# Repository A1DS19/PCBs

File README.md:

# PCB Designs

A collection of printed circuit board (PCB) designs for various projects.

## Overview

This repository contains PCB design files, schematics, and documentation for custom electronic circuits.

## PCB Process:
1. Place components
2. Create board outline (Edge.Cuts)
3. Export DSN to Freerouting
4. Autoroute in Freerouting
5. Import SES file back to KiCad
6. THEN add copper pours (last step!)
7. Fill zones (B key)
8. Add vias for ground plane stitching
9. Run final DRC

## Getting Started

### Prerequisites
- [KiCad](https://www.kicad.org/) - Open source EDA software

### Manufacturing
- [JLCPCB](https://jlcpcb.com/)

- Vid: 3:36:29

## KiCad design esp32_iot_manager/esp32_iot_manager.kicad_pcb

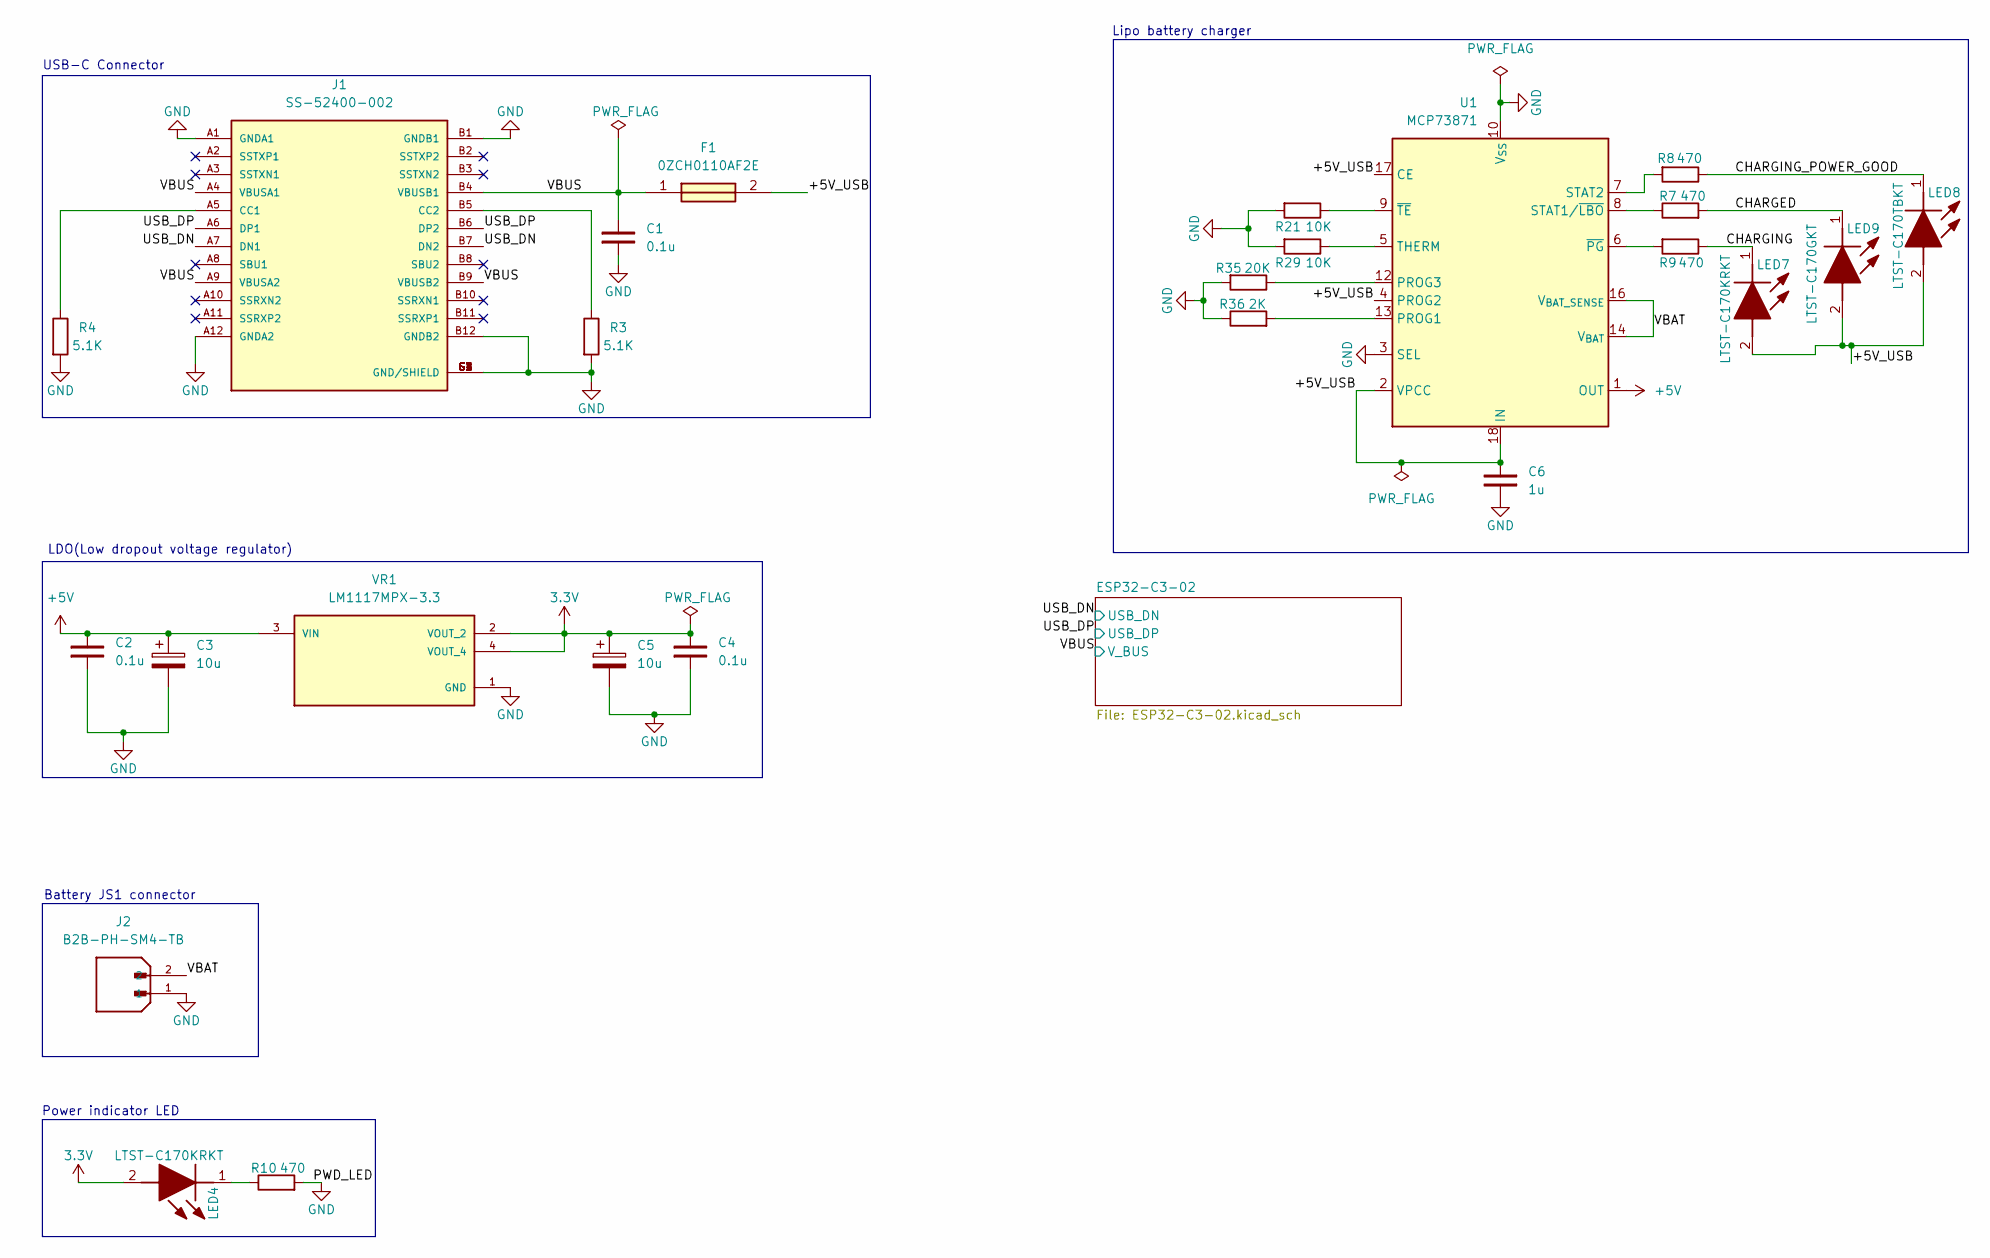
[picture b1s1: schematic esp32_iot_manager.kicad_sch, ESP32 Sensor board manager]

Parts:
C1, C2, C4: 0.1u; C_0805_2012Metric
C3, C5: 10u; T491A
C6: 1u; C_Disc_D3.0mm_W2.0mm_P2.50mm
F1: 0ZCH0110AF2E; FUSC3226X100N; Manufacturer_Part_Number 0ZCH0110AF2E
J1: SS-52400-002; BELFUSE_SS-52400-002; PARTREV A0
J2: B2B-PH-SM4-TB; JST_B2B-PH-SM4-TB; PARTREV N/A
LED4, LED7: LTST-C170KRKT; LEDC2012X120N; Manufacturer_Part_Number LTST-C170KRKT; Mouser Part Number 859-LTST-C170KRKT
LED8: LTST-C170TBKT; LEDC2012X120N; Manufacturer_Part_Number LTST-C170TBKT; Mouser Part Number 859-LTST-C170TBKT
LED9: LTST-C170GKT; LEDC2012X120N; Manufacturer_Part_Number LTST-C170GKT; Mouser Part Number 859-LTST-C170GKT
R3, R4: 5.1K; R_0805_2012Metric
R7, R8, R9, R10: 470; R_0805_2012Metric
R21, R29: 10K; R_0805_2012Metric
R35: 20K; R_0805_2012Metric
R36: 2K; R_0805_2012Metric
U1: MCP73871; QFN-20-1EP_4x4mm_P0.5mm_EP2.5x2.5mm
VR1: LM1117MPX-3.3; VREG_LM1117MPX-3.3

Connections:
3.3V: C4.2, C5.1, LED4.2 (A), VR1.2 (VOUT_2), VR1.4 (VOUT_4); also elsewhere on the board
+5V: C2.2, C3.1, U1.1 (OUT), U1.20 (OUT), VR1.3 (VIN); also elsewhere on the board
/+5V_USB: C6.1, F1.2, LED7.2 (A), LED8.2 (A), LED9.2 (A), U1.2 (VPCC), U1.4 (PROG2), U1.17 (CE), U1.18 (IN), U1.19 (IN)
/CHARGED: LED9.1 (K), R7.2
/CHARGING: LED7.1 (K), R9.1
/CHARGING_POWER_GOOD: LED8.1 (K), R8.1
/USB_DN: J1.A7 (DN1), J1.B7 (DN2); also elsewhere on the board
/USB_DP: J1.A6 (DP1), J1.B6 (DP2); also elsewhere on the board
/VBAT: J2.2, U1.14 (V_{BAT}), U1.15 (V_{BAT}), U1.16 (V_{BAT_SENSE})
/VBUS: C1.2, F1.1, J1.A4 (VBUSA1), J1.A9 (VBUSA2), J1.B4 (VBUSB1), J1.B9 (VBUSB2); also elsewhere on the board
GND: C1.1, C2.1, C3.2, C4.1, C5.2, C6.2, J1.A1 (GNDA1), J1.A12 (GNDA2), J1.B1 (GNDB1), J1.B12 (GNDB2), J1.G1 (GND/SHIELD), J1.G2 (GND/SHIELD), J1.G3 (GND/SHIELD), J1.G4 (GND/SHIELD), J1.S1 (GND/SHIELD), J1.S2 (GND/SHIELD), J1.S3 (GND/SHIELD), J1.S4 (GND/SHIELD), J2.1, R3.2, R4.2, R10.2, R21.2, R29.2, R35.2, R36.1, U1.3 (SEL), U1.10 (V_{SS}), U1.11 (V_{SS}), U1.21 (V_{SS}), VR1.1 (GND); also elsewhere on the board
unnamed: J1.A5 (CC1), R4.1
unnamed: J1.B5 (CC2), R3.1
unnamed: LED4.1 (K), R10.1
unnamed: R36.2, U1.13 (PROG1)
unnamed: R35.1, U1.12 (PROG3)
unnamed: R7.1, U1.8 (STAT1/~LBO)
unnamed: R8.2, U1.7 (STAT2)
unnamed: R29.1, U1.5 (THERM)
unnamed: R9.2, U1.6 (~PG)
unnamed: R21.1, U1.9 (~TE)

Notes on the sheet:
Battery JS1 connector
Power indicator LED
Lipo battery charger
USB-C Connector
LDO(Low dropout voltage regulator)

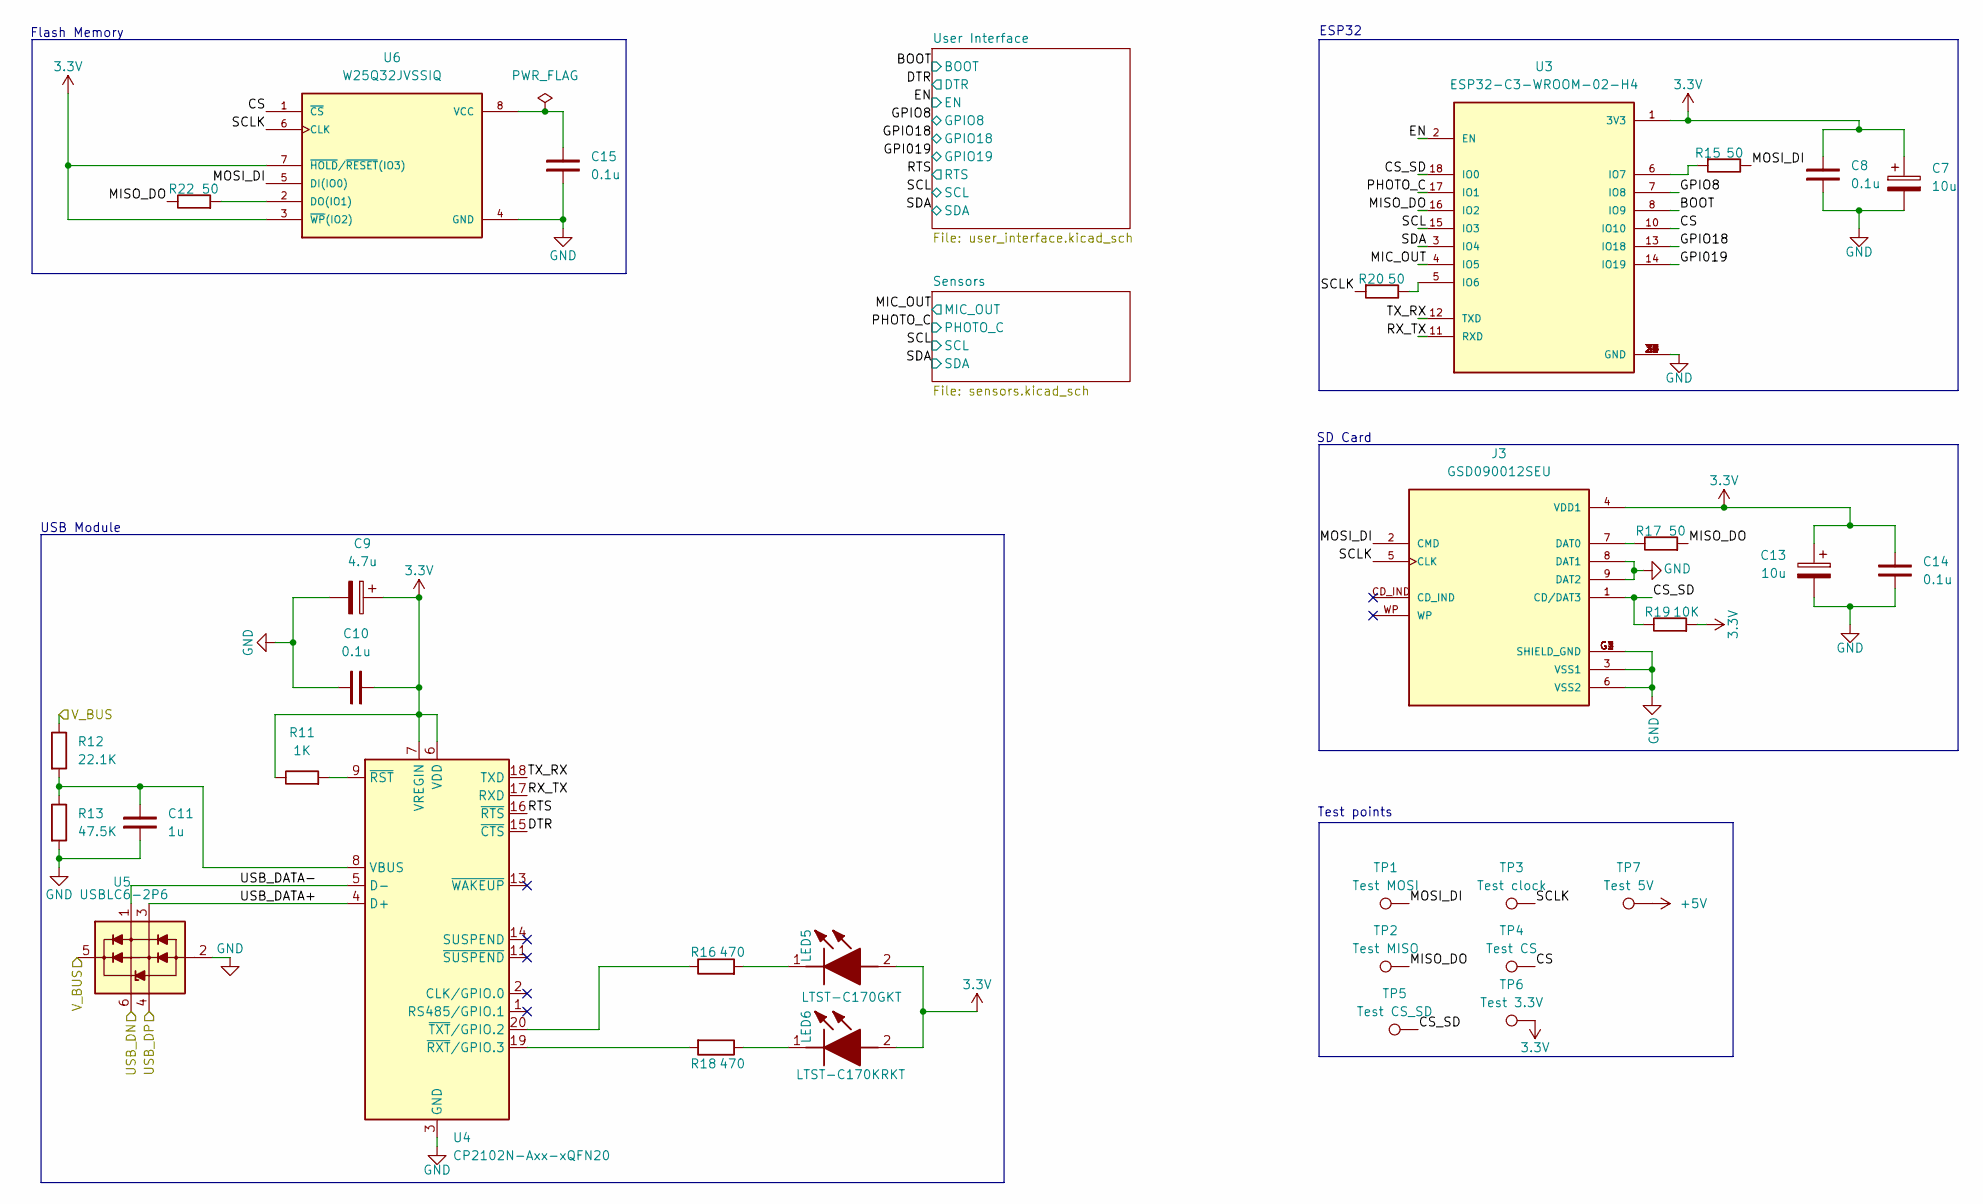
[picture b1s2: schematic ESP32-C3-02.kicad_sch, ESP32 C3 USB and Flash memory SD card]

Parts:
C7, C13: 10u; T491A
C8, C10, C14, C15: 0.1u; C_0805_2012Metric
C9: 4.7u; T491A
C11: 1u; C_0805_2012Metric
J3: GSD090012SEU; AMPHENOL_GSD090012SEU; PARTREV E
LED5: LTST-C170GKT; LEDC2012X120N; Manufacturer_Part_Number LTST-C170GKT; Mouser Part Number 859-LTST-C170GKT
LED6: LTST-C170KRKT; LEDC2012X120N; Manufacturer_Part_Number LTST-C170KRKT; Mouser Part Number 859-LTST-C170KRKT
R11: 1K; R_0805_2012Metric
R12: 22.1K; R_0805_2012Metric
R13: 47.5K; R_0805_2012Metric
R15, R17, R20, R22: 50; R_0805_2012Metric
R16, R18: 470; R_0805_2012Metric
R19: 10K; R_0805_2012Metric
TP1: Test MOSI; TestPoint_Pad_D1.0mm
TP2: Test MISO; TestPoint_Pad_D1.0mm
TP3: Test clock; TestPoint_Pad_D1.0mm
TP4: Test CS; TestPoint_Pad_D1.0mm
TP5: Test CS_SD; TestPoint_Pad_D1.0mm
TP6: Test 3.3V; TestPoint_Pad_D1.0mm
TP7: Test 5V; TestPoint_Pad_D1.0mm
U3: ESP32-C3-WROOM-02-H4; MODULE_ESP32-C3-WROOM-02-H4
U4: CP2102N-Axx-xQFN20; SiliconLabs_QFN-20-1EP_3x3mm_P0.5mm
U5: USBLC6-2P6; SOT-666
U6: W25Q32JVSSIQ; SOIC127P790X216-8N; M_PART_NUMBER W25QXX

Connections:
3.3V: C7.1, C8.2, C9.1, C10.1, C13.1, C14.1, J3.4 (VDD1), LED5.2 (A), LED6.2 (A), R11.2, R19.1, TP6.1, U3.1 (3V3), U4.6 (VDD), U4.7 (VREGIN), U6.3 (~WP(IO2)), U6.7 (~HOLD/~RESET(IO3)); also elsewhere on the board
+5V: TP7.1; also elsewhere on the board
/ESP32-C3-02/BOOT: U3.8 (IO9); also elsewhere on the board
/ESP32-C3-02/CS: TP4.1, U3.10 (IO10), U6.1 (~CS)
/ESP32-C3-02/CS_SD: J3.1 (CD/DAT3), R19.2, TP5.1, U3.18 (IO0)
/ESP32-C3-02/DTR: U4.15 (~CTS); also elsewhere on the board
/ESP32-C3-02/EN: U3.2 (EN); also elsewhere on the board
/ESP32-C3-02/GPI019: U3.14 (IO19); also elsewhere on the board
/ESP32-C3-02/GPIO8: U3.7 (IO8); also elsewhere on the board
/ESP32-C3-02/GPIO18: U3.13 (IO18); also elsewhere on the board
/ESP32-C3-02/MIC_OUT: U3.4 (IO5); also elsewhere on the board
/ESP32-C3-02/MISO_DO: R17.1, R22.2, TP2.1, U3.16 (IO2)
/ESP32-C3-02/MOSI_DI: J3.2 (CMD), R15.2, TP1.1, U6.5 (DI(IO0))
/ESP32-C3-02/PHOTO_C: U3.17 (IO1); also elsewhere on the board
/ESP32-C3-02/RTS: U4.16 (~RTS); also elsewhere on the board
/ESP32-C3-02/RX_TX: U3.11 (RXD), U4.17 (RXD)
/ESP32-C3-02/SCL: U3.15 (IO3); also elsewhere on the board
/ESP32-C3-02/SCLK: J3.5 (CLK), R20.1, TP3.1, U6.6 (CLK)
/ESP32-C3-02/SDA: U3.3 (IO4); also elsewhere on the board
/ESP32-C3-02/TX_RX: U3.12 (TXD), U4.18 (TXD)
/ESP32-C3-02/USB_DATA+: U4.4 (D+), U5.3 (L2)
/ESP32-C3-02/USB_DATA-: U4.5 (D-), U5.1 (L1)
/USB_DN: U5.6 (L1); also elsewhere on the board
/USB_DP: U5.4 (L2); also elsewhere on the board
/VBUS: R12.1, U5.5 (VP); also elsewhere on the board
GND: C7.2, C8.1, C9.2, C10.2, C11.1, C13.2, C14.2, C15.1, J3.3 (VSS1), J3.6 (VSS2), J3.8 (DAT1), J3.9 (DAT2), J3.G1 (SHIELD_GND), J3.G2 (SHIELD_GND), J3.G3 (SHIELD_GND), J3.G4 (SHIELD_GND), R13.2, U3.9 (GND), U3.19 (GND), U3.20 (GND), U3.21 (GND), U3.22 (GND), U3.23 (GND), U3.24 (GND), U3.25 (GND), U3.26 (GND), U3.27 (GND), U3.28 (GND), U3.29 (GND), U3.30 (GND), U3.31 (GND), U3.32 (GND), U3.33 (GND), U3.34 (GND), U3.35 (GND), U3.36 (GND), U3.37 (GND), U3.38 (GND), U3.39 (GND), U4.3 (GND), U4.12 (GND), U4.21 (GND), U5.2 (VN), U6.4 (GND); also elsewhere on the board
unnamed: J3.7 (DAT0), R17.2
unnamed: LED5.1 (K), R16.2
unnamed: LED6.1 (K), R18.1
unnamed: R20.2, U3.5 (IO6)
unnamed: R15.1, U3.6 (IO7)
unnamed: C11.2, R12.2, R13.1, U4.8 (VBUS)
unnamed: R11.1, U4.9 (~RST)
unnamed: R18.2, U4.19 (~RXT/GPIO.3)
unnamed: R16.1, U4.20 (~TXT/GPIO.2)
unnamed: R22.1, U6.2 (DO(IO1))
unnamed: C15.2, U6.8 (VCC)

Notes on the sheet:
ESP32
SD Card
USB Module
Flash Memory
Test points

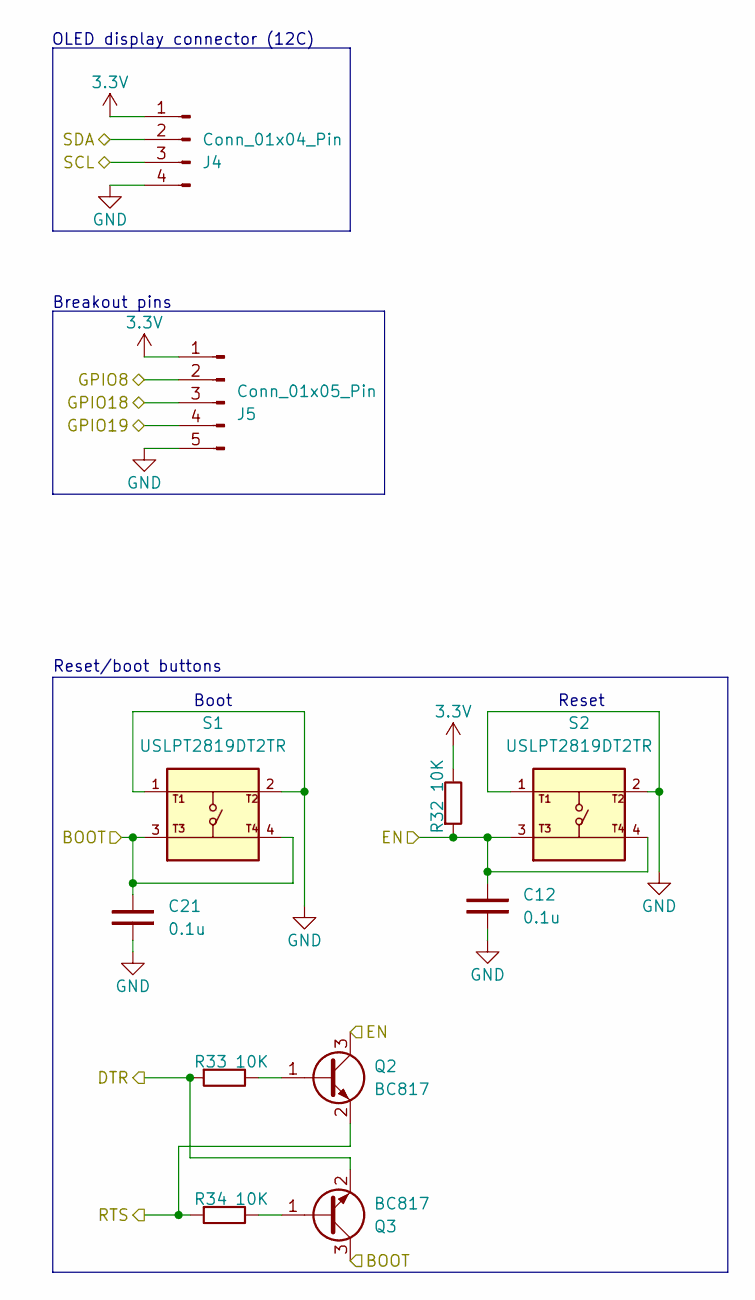
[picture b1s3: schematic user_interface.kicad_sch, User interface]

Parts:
C12, C21: 0.1u; C_0805_2012Metric
J4: Conn_01x04_Pin; PinHeader_1x04_P2.54mm_Vertical
J5: Conn_01x05_Pin; PinHeader_1x05_P2.54mm_Vertical
Q2, Q3: BC817; SOT-23
R32, R33, R34: 10K; R_0805_2012Metric
S1, S2: USLPT2819DT2TR; SW_USLPT2819DT2TR; PARTREV P

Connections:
3.3V: J4.1, J5.1, R32.2; also elsewhere on the board
/ESP32-C3-02/BOOT: C21.1, Q3.3 (C), S1.3, S1.4; also elsewhere on the board
/ESP32-C3-02/DTR: Q3.2 (E), R33.1; also elsewhere on the board
/ESP32-C3-02/EN: C12.1, Q2.3 (C), R32.1, S2.3, S2.4; also elsewhere on the board
/ESP32-C3-02/GPI019: J5.4; also elsewhere on the board
/ESP32-C3-02/GPIO8: J5.2; also elsewhere on the board
/ESP32-C3-02/GPIO18: J5.3; also elsewhere on the board
/ESP32-C3-02/RTS: Q2.2 (E), R34.1; also elsewhere on the board
/ESP32-C3-02/SCL: J4.3; also elsewhere on the board
/ESP32-C3-02/SDA: J4.2; also elsewhere on the board
GND: C12.2, C21.2, J4.4, J5.5, S1.1, S1.2, S2.1, S2.2; also elsewhere on the board
unnamed: Q2.1 (B), R33.2
unnamed: Q3.1 (B), R34.2

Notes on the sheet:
OLED display connector (12C)
Breakout pins
Boot
Reset/boot buttons
Reset

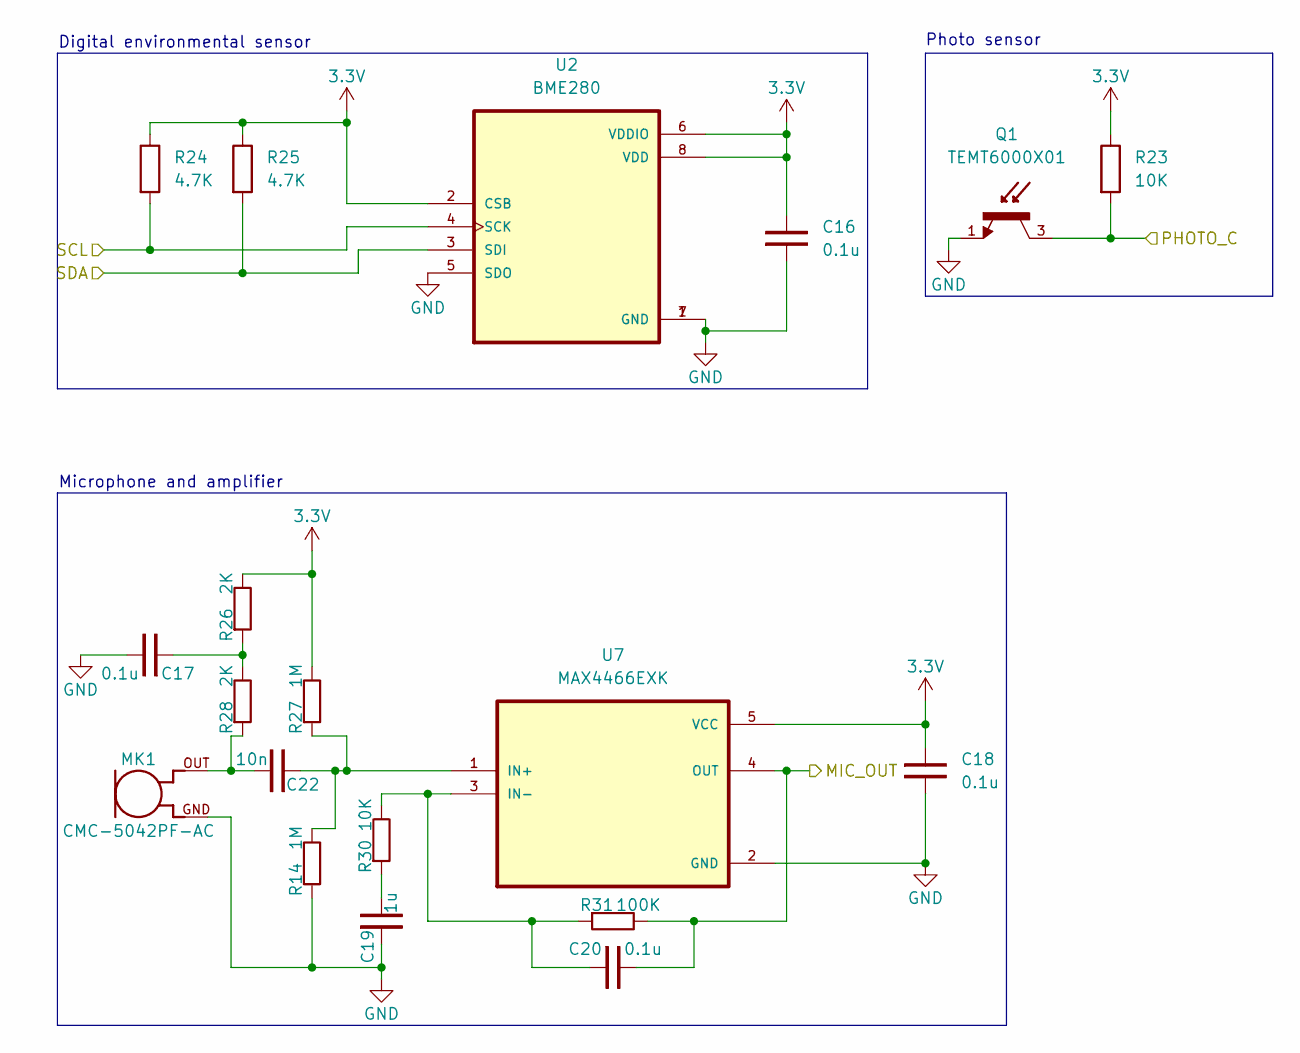
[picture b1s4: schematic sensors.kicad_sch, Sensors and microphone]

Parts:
C16, C17, C18, C20: 0.1u; C_0805_2012Metric
C19: 1u; C_0805_2012Metric
C22: 10n; C_0805_2012Metric
MK1: CMC-5042PF-AC; CUI_CMC-5042PF-AC
Q1: TEMT6000X01; TRANS_TEMT6000X01; PARTREV 1.9
R14, R27: 1M; R_0805_2012Metric
R23, R30: 10K; R_0805_2012Metric
R24, R25: 4.7K; R_0805_2012Metric
R26, R28: 2K; R_0805_2012Metric
R31: 100K; R_0805_2012Metric
U2: BME280; PSON65P250X250X100-8N
U7: MAX4466EXK; SOT65P210X110-5N

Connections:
3.3V: C16.2, C18.2, R23.1, R24.1, R25.1, R26.2, R27.2, U2.2 (CSB), U2.6 (VDDIO), U2.8 (VDD), U7.5 (VCC); also elsewhere on the board
/ESP32-C3-02/MIC_OUT: C20.2, R31.2, U7.4 (OUT); also elsewhere on the board
/ESP32-C3-02/PHOTO_C: Q1.3, R23.2; also elsewhere on the board
/ESP32-C3-02/SCL: R24.2, U2.4 (SCK); also elsewhere on the board
/ESP32-C3-02/SDA: R25.2, U2.3 (SDI); also elsewhere on the board
GND: C16.1, C17.2, C18.1, C19.1, MK1.GND, Q1.1, R14.1, U2.1 (GND), U2.5 (SDO), U2.7 (GND), U7.2 (GND); also elsewhere on the board
unnamed: C17.1, R26.1, R28.2
unnamed: C19.2, R30.1
unnamed: C22.2, MK1.OUT, R28.1
unnamed: C22.1, R14.2, R27.1, U7.1 (IN+)
unnamed: C20.1, R30.2, R31.1, U7.3 (IN-)

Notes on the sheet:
Digital environmental sensor
Photo sensor
Microphone and amplifier

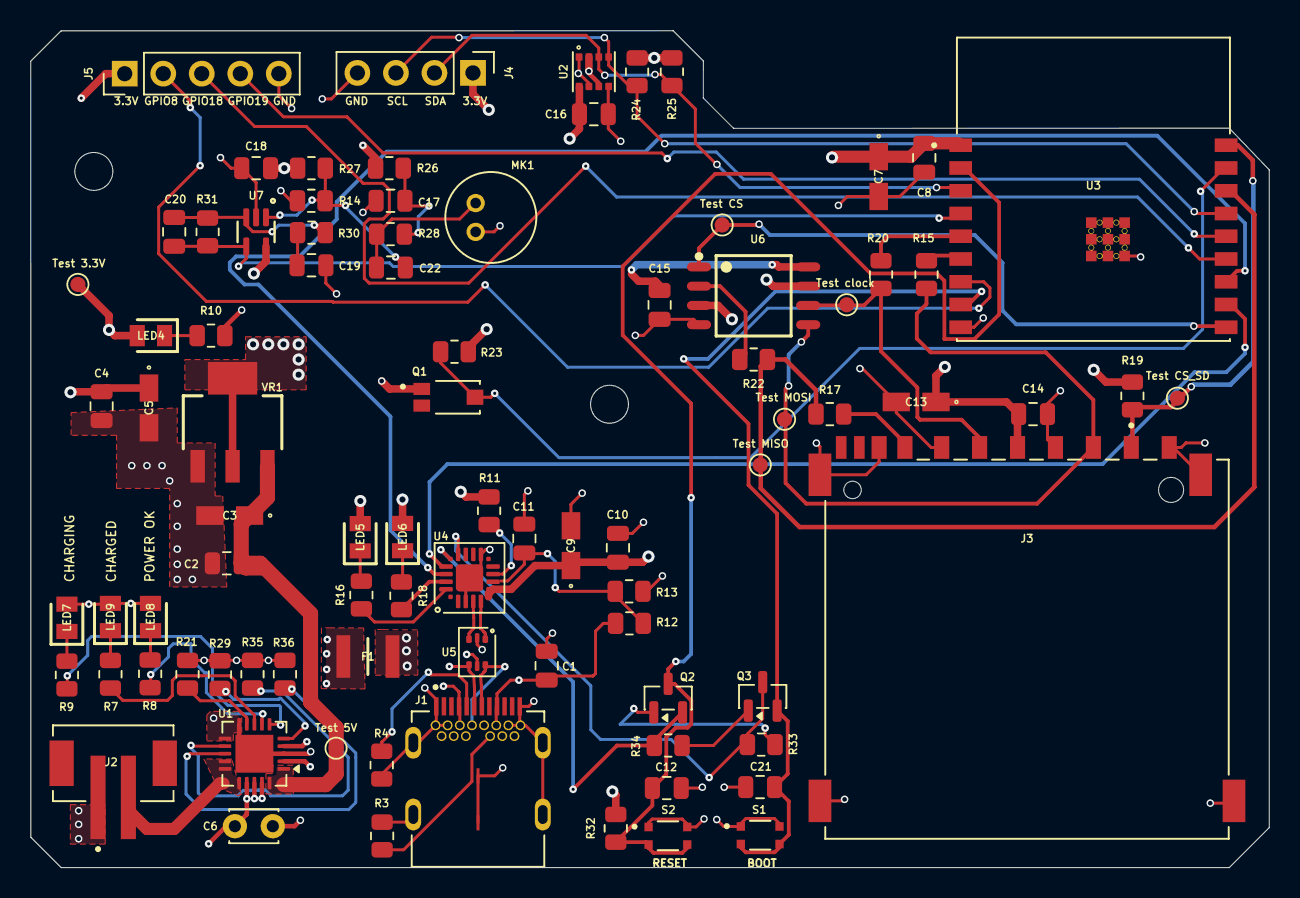
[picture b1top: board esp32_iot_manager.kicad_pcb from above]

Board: 4 copper layers, 81.7 x 55.2 mm, 87 parts (0 on the bottom side), 59 nets.

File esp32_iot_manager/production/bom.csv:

Designator,Footprint,Quantity,Value,LCSC Part #
"C1, C10, C12, C14, C15, C16, C17, C18, C2, C20, C21, C4, C8",0805,13,0.1u,
"C11, C19",0805,2,1u,
"C13, C3, C5, C7",T491A,4,10u,
C22,0805,1,10n,
C6,C_Disc_D3.0mm_W2.0mm_P2.50mm,1,1u,
C9,T491A,1,4.7u,
F1,FUSC3226X100N,1,0ZCH0110AF2E,
J1,BELFUSE_SS-52400-002,1,SS-52400-002,
J2,JST_B2B-PH-SM4-TB,1,B2B-PH-SM4-TB,
J3,AMPHENOL_GSD090012SEU,1,GSD090012SEU,
J4,PinHeader_1x04_P2.54mm_Vertical,1,Conn_01x04_Pin,
J5,PinHeader_1x05_P2.54mm_Vertical,1,Conn_01x05_Pin,
"LED4, LED6, LED7",LEDC2012X120N,3,LTST-C170KRKT,
"LED5, LED9",LEDC2012X120N,2,LTST-C170GKT,
LED8,LEDC2012X120N,1,LTST-C170TBKT,
MK1,CUI_CMC-5042PF-AC,1,CMC-5042PF-AC,
Q1,TRANS_TEMT6000X01,1,TEMT6000X01,
"Q2, Q3",SOT-23,2,BC817,
"R10, R16, R18, R7, R8, R9",0805,6,470,
R11,0805,1,1K,
R12,0805,1,22.1K,
R13,0805,1,47.5K,
"R14, R27",0805,2,1M,
"R15, R17, R20, R22",0805,4,50,
"R19, R21, R23, R29, R30, R32, R33, R34",0805,8,10K,
"R24, R25",0805,2,4.7K,
"R26, R28, R36",0805,3,2K,
"R3, R4",0805,2,5.1K,
R31,0805,1,100K,
R35,0805,1,20K,
"S1, S2",SW_USLPT2819DT2TR,2,USLPT2819DT2TR,
TP1,TestPoint_Pad_D1.0mm,1,MOSI,
TP2,TestPoint_Pad_D1.0mm,1, MISO,
TP3,TestPoint_Pad_D1.0mm,1,CLOCK,
TP4,TestPoint_Pad_D1.0mm,1,CS,
TP5,TestPoint_Pad_D1.0mm,1,CS_SD,
TP6,TestPoint_Pad_D1.0mm,1,3.3V,
TP7,TestPoint_Pad_D1.0mm,1,5V,
U1,QFN-20-1EP_4x4mm_P0.5mm_EP2.5x2.5mm,1,MCP73871,
U2,PSON65P250X250X100-8N,1,BME280,
U3,MODULE_ESP32-C3-WROOM-02-H4,1,ESP32-C3-WROOM-02-H4,
U4,SiliconLabs_QFN-20-1EP_3x3mm_P0.5mm,1,CP2102N-Axx-xQFN20,
U5,SOT-666,1,USBLC6-2P6,
U6,SOIC127P790X216-8N,1,W25Q32JVSSIQ,
U7,SOT65P210X110-5N,1,MAX4466EXK,
VR1,VREG_LM1117MPX-3.3,1,LM1117MPX-3.3,

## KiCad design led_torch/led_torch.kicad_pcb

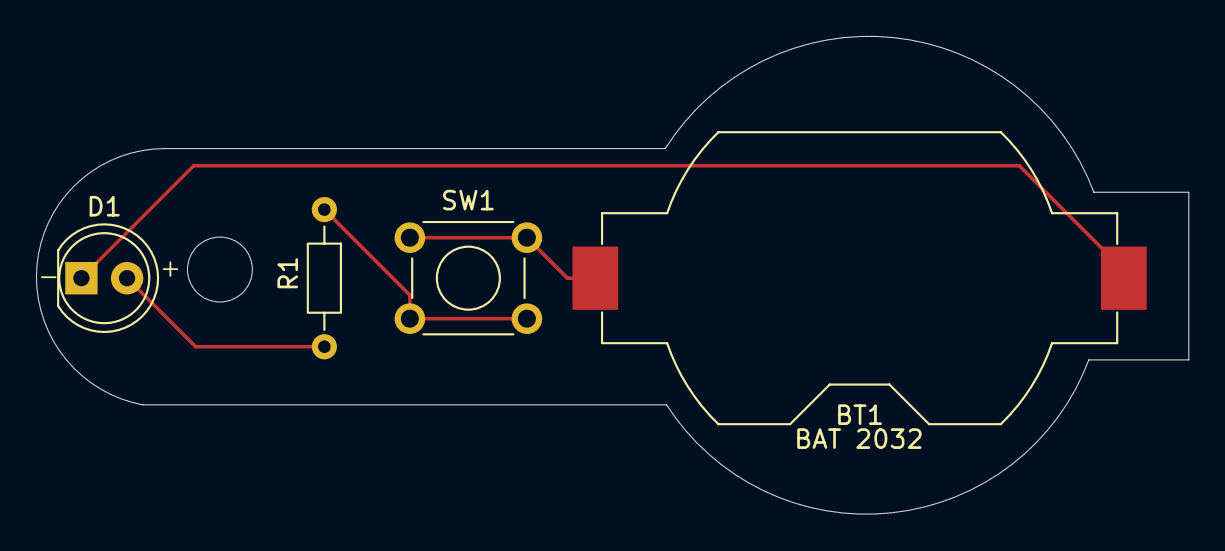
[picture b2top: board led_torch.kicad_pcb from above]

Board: 2 copper layers, 64.0 x 26.5 mm, 4 parts (0 on the bottom side), 4 nets.

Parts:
BT1: BAT 2032; BatteryHolder_Keystone_1058_1x2032
D1: LED; LED_D5.0mm
R1: R; R_Axial_DIN0204_L3.6mm_D1.6mm_P7.62mm_Horizontal
SW1: SW_DPDT_x2; SW_TH_Tactile_Omron_B3F-100x

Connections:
/BAT+: BT1.1 (+), SW1.1 (A)
/LED_ANODE: D1.2 (A), R1.2
/LED_CATHODE: BT1.2 (-), D1.1 (K)
unnamed: R1.1, SW1.2 (B)

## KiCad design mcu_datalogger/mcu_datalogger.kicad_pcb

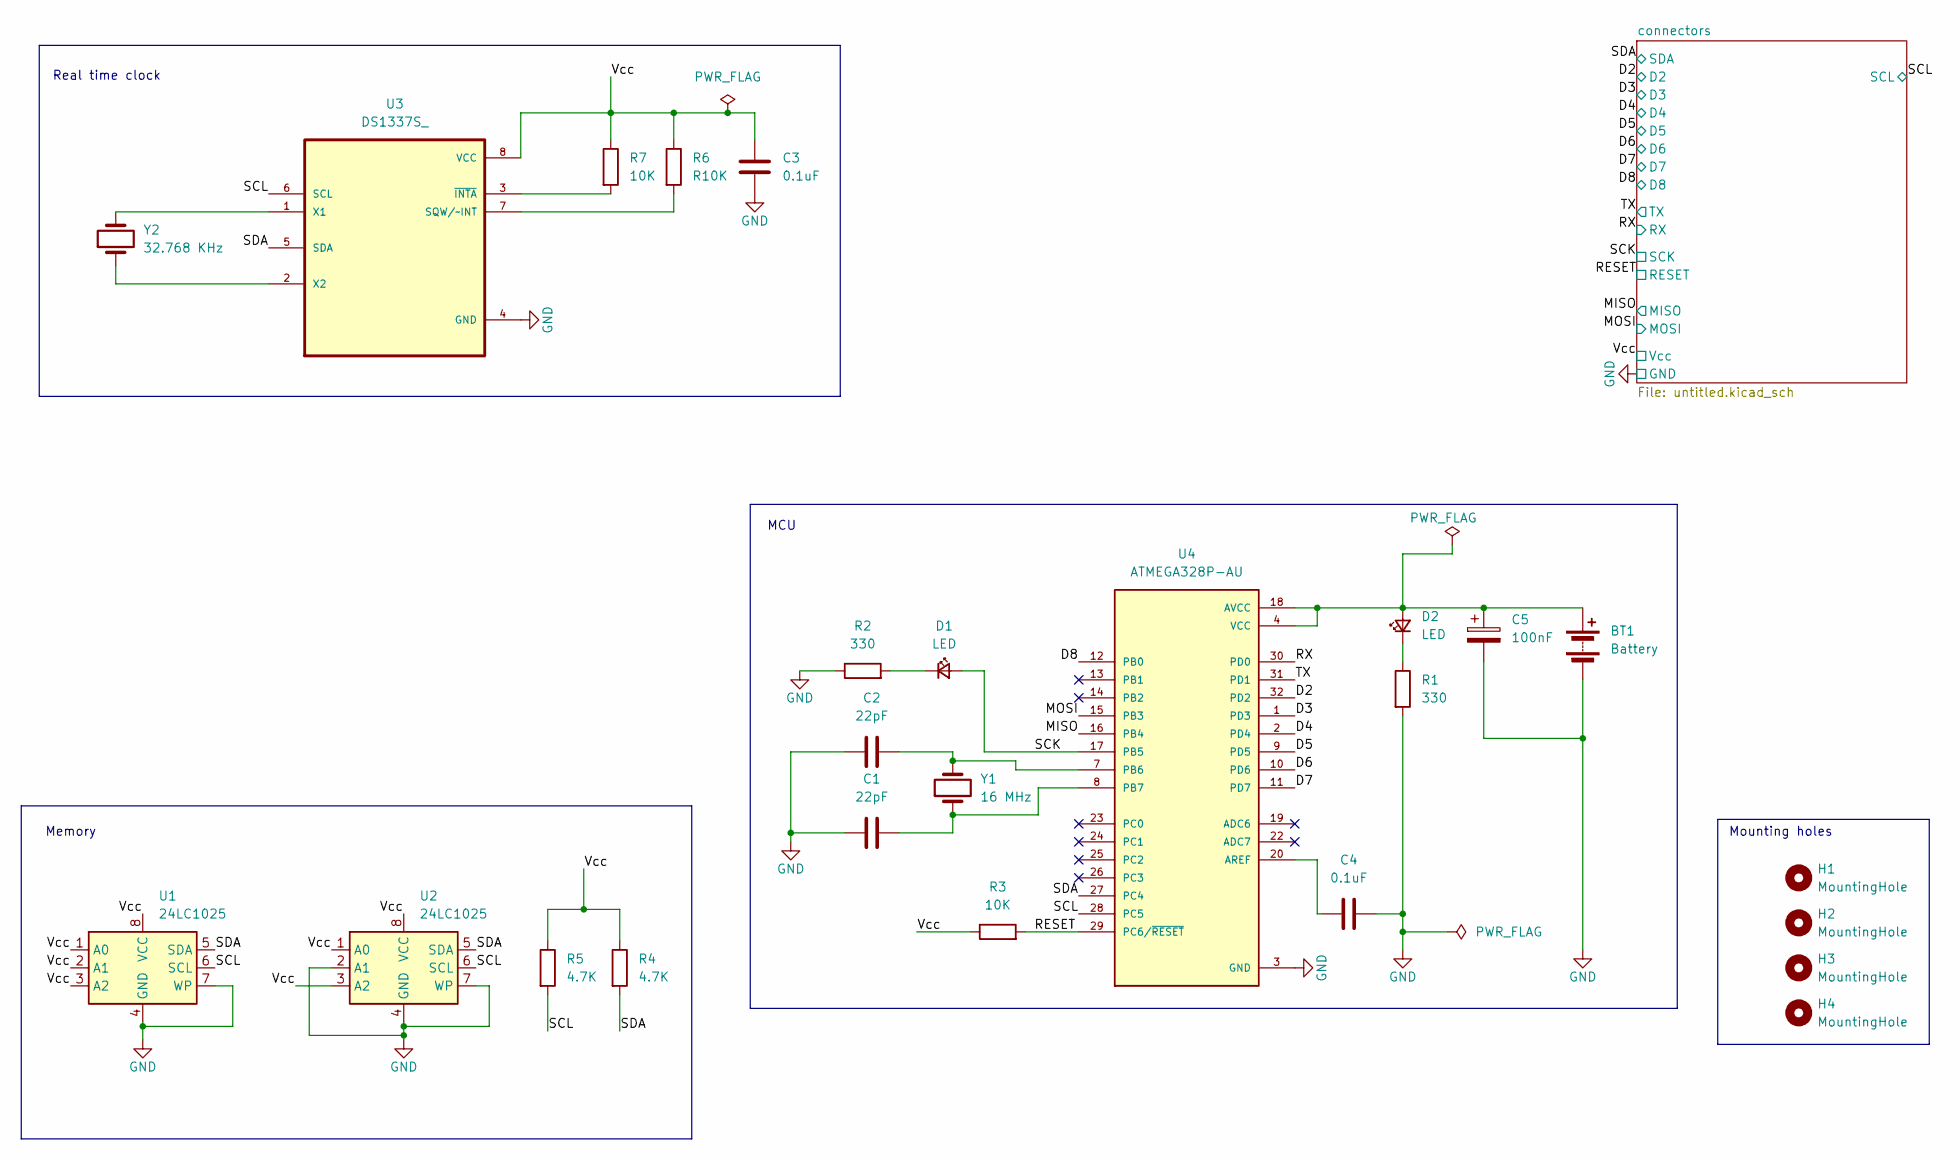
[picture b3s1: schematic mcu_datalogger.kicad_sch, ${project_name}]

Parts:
BT1: Battery; PinHeader_1x02_P2.54mm_Vertical
C1, C2: 22pF; C_0805_2012Metric
C3, C4: 0.1uF; C_0805_2012Metric
C5: 100nF; C_0805_2012Metric
D1, D2: LED; LED_0805_2012Metric
H1, H2, H3, H4: MountingHole; MountingHole_2.1mm
R1, R2: 330; R_0805_2012Metric
R3, R7: 10K; R_0805_2012Metric
R4, R5: 4.7K; R_0805_2012Metric
R6: R10K; R_0805_2012Metric
U1, U2: 24LC1025; SOIC-8_5.3x5.3mm_P1.27mm
U3: DS1337S_; SOIC127P600X175-8N
U4: ATMEGA328P-AU; QFP80P900X900X120-32N; PARTREV 8271A
Y1: 16 MHz; Crystal_SMD_5032-2Pin_5.0x3.2mm
Y2: 32.768 KHz; Crystal_SMD_5032-2Pin_5.0x3.2mm

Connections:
/D2: U4.32 (PD2); also elsewhere on the board
/D3: U4.1 (PD3); also elsewhere on the board
/D4: U4.2 (PD4); also elsewhere on the board
/D5: U4.9 (PD5); also elsewhere on the board
/D6: U4.10 (PD6); also elsewhere on the board
/D7: U4.11 (PD7); also elsewhere on the board
/D8: U4.12 (PB0); also elsewhere on the board
/MISO: U4.16 (PB4); also elsewhere on the board
/MOSI: U4.15 (PB3); also elsewhere on the board
/RESET: R3.2, U4.29 (PC6/~RESET); also elsewhere on the board
/RX: U4.30 (PD0); also elsewhere on the board
/SCK: D1.2 (A), U4.17 (PB5); also elsewhere on the board
/SCL: R5.2, U1.6 (SCL), U2.6 (SCL), U3.6 (SCL), U4.28 (PC5); also elsewhere on the board
/SDA: R4.2, U1.5 (SDA), U2.5 (SDA), U3.5 (SDA), U4.27 (PC4); also elsewhere on the board
/TX: U4.31 (PD1); also elsewhere on the board
/Vcc: C3.1, R3.1, R4.1, R5.1, R6.1, R7.1, U1.1 (A0), U1.2 (A1), U1.3 (A2), U1.8 (VCC), U2.1 (A0), U2.3 (A2), U2.8 (VCC), U3.8 (VCC); also elsewhere on the board
GND: BT1.2 (-), C1.1, C2.1, C3.2, C4.2, C5.2, R1.2, R2.1, U1.4 (GND), U1.7 (WP), U2.2 (A1), U2.4 (GND), U2.7 (WP), U3.4 (GND), U4.3 (GND), U4.5 (GND), U4.21 (GND); also elsewhere on the board
unnamed: D1.1 (K), R2.2
unnamed: D2.1 (K), R1.1
unnamed: R6.2, U3.7 (SQW/~INT)
unnamed: U3.1 (X1), Y2.2
unnamed: U3.2 (X2), Y2.1
unnamed: R7.2, U3.3 (~INTA)
unnamed: C4.1, U4.20 (AREF)
unnamed: C2.2, U4.7 (PB6), Y1.2
unnamed: C1.2, U4.8 (PB7), Y1.1
VCC: BT1.1 (+), C5.1, D2.2 (A), U4.4 (VCC), U4.6 (VCC), U4.18 (AVCC)

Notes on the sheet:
Real time clock
MCU
Mounting holes
Memory

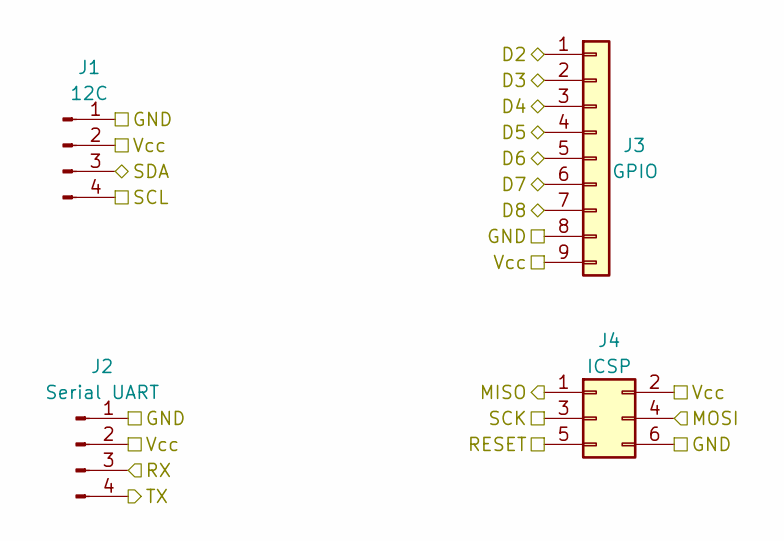
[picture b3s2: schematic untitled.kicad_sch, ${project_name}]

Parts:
J1, J2: Conn_01x04_Pin; PinHeader_1x04_P2.54mm_Vertical
J3: Conn_01x09; PinHeader_1x09_P2.54mm_Vertical
J4: Conn_02x03_Odd_Even; PinHeader_2x03_P2.54mm_Vertical

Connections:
/D2: J3.1; also elsewhere on the board
/D3: J3.2; also elsewhere on the board
/D4: J3.3; also elsewhere on the board
/D5: J3.4; also elsewhere on the board
/D6: J3.5; also elsewhere on the board
/D7: J3.6; also elsewhere on the board
/D8: J3.7; also elsewhere on the board
/MISO: J4.1; also elsewhere on the board
/MOSI: J4.4; also elsewhere on the board
/RESET: J4.5; also elsewhere on the board
/RX: J2.3; also elsewhere on the board
/SCK: J4.3; also elsewhere on the board
/SCL: J1.4; also elsewhere on the board
/SDA: J1.3; also elsewhere on the board
/TX: J2.4; also elsewhere on the board
/Vcc: J1.2, J2.2, J3.9, J4.2; also elsewhere on the board
GND: J1.1, J2.1, J3.8, J4.6; also elsewhere on the board

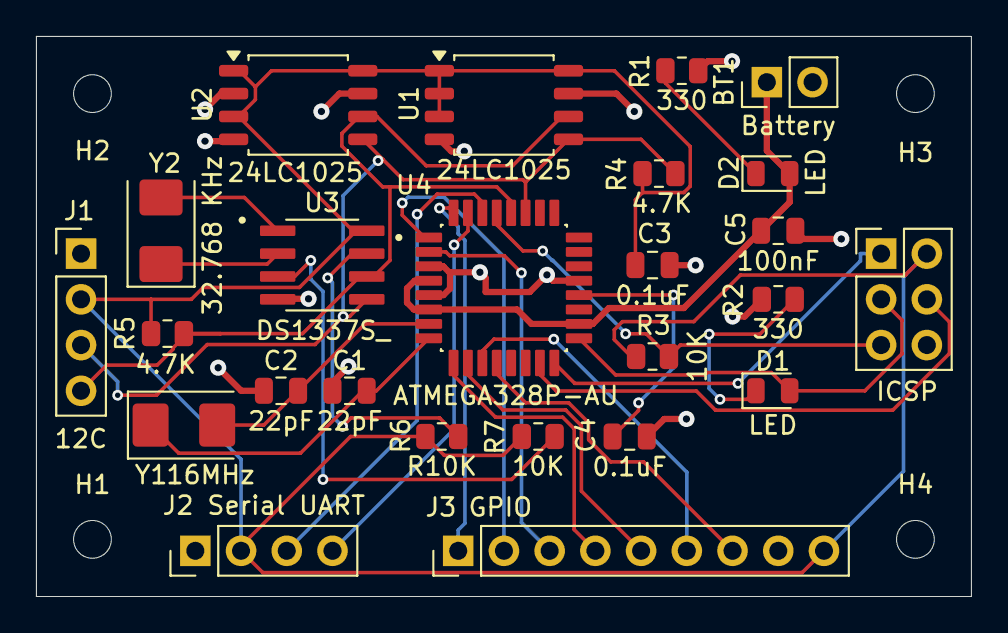
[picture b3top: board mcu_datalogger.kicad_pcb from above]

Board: 2 copper layers, 51.9 x 31.1 mm, 29 parts (0 on the bottom side), 27 nets.

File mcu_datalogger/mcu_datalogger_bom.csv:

"Id";"Designator";"Footprint";"Quantity";"Designation";"Supplier and ref";
1;"Y1";"Crystal_SMD_5032-2Pin_5.0x3.2mm";1;"16MHz";;;
2;"R6";"R_0805_2012Metric";1;"R10K";;;
3;"BT1";"PinHeader_1x02_P2.54mm_Vertical";1;"Battery";;;
4;"C1,C2";"C_0805_2012Metric";2;"22pF";;;
5;"J4";"PinHeader_2x03_P2.54mm_Vertical";1;"Conn_02x03_Odd_Even";;;
6;"J3";"PinHeader_1x09_P2.54mm_Vertical";1;"Conn_01x09";;;
7;"C3,C4";"C_0805_2012Metric";2;"0.1uF";;;
8;"R5,R4";"R_0805_2012Metric";2;"4.7K";;;
9;"Y2";"Crystal_SMD_5032-2Pin_5.0x3.2mm";1;"32.768 KHz";;;
10;"R2,R1";"R_0805_2012Metric";2;"330";;;
11;"D1,D2";"LED_0805_2012Metric";2;"LED";;;
12;"U2,U1";"SOIC-8_5.3x5.3mm_P1.27mm";2;"24LC1025";;;
13;"U3";"SOIC127P600X175-8N";1;"DS1337S_";;;
14;"J2,J1";"PinHeader_1x04_P2.54mm_Vertical";2;"Conn_01x04_Pin";;;
15;"R3,R7";"R_0805_2012Metric";2;"10K";;;
16;"U4";"QFP80P900X900X120-32N";1;"ATMEGA328P-AU";;;
17;"C5";"C_0805_2012Metric";1;"100nF";;;

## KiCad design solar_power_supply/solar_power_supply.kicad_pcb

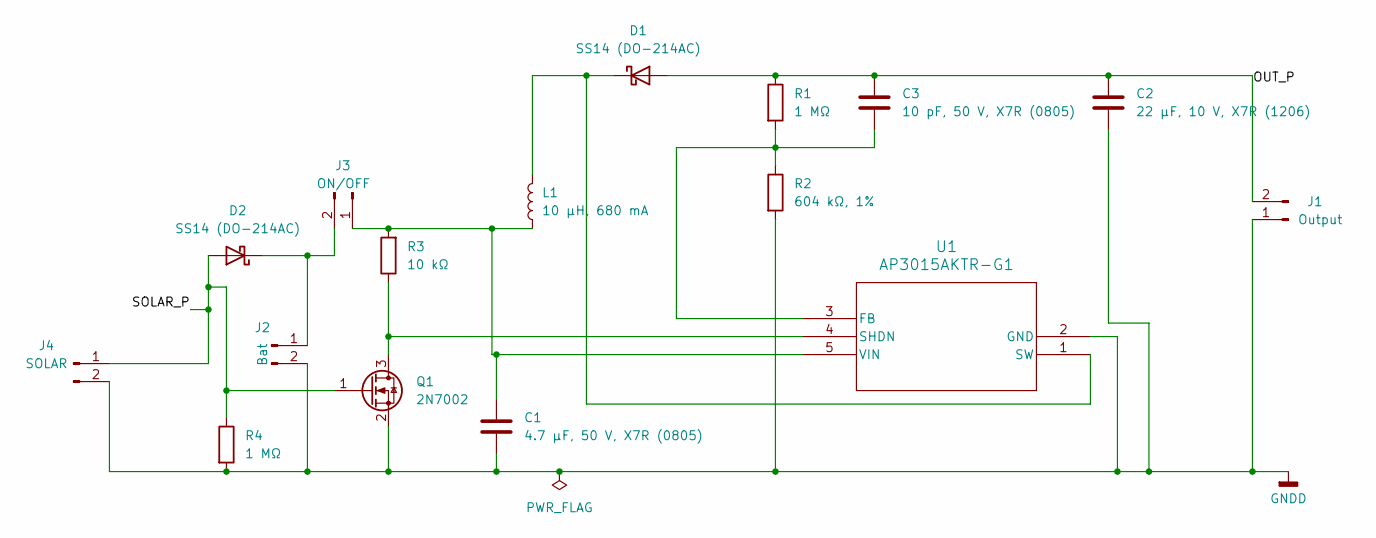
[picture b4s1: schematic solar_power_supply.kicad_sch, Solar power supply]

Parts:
C1: 4.7 µF, 50 V, X7R (0805); C_0805_2012Metric
C2: 22 µF, 10 V, X7R (1206); C_1206_3216Metric
C3: 10 pF, 50 V, X7R (0805); C_0805_2012Metric
D1, D2: SS14 (DO-214AC); D_SMA
J1, J2, J3: Conn_01x02_Pin; PinHeader_1x02_P2.54mm_Vertical
J4: Conn_01x02_Pin; PinHeader_1x02_P2.54mm_Horizontal
L1: 10 µH, 680 mA; L_Abracon_ASPI-0630LR
Q1: 2N7002; SOT-23
R1, R4: 1 MΩ; R_0805_2012Metric
R2: 604 kΩ, 1%; R_0805_2012Metric
R3: 10 kΩ; R_0805_2012Metric
U1: AP3015AKTR-G1; SOT23-5_1P55X2P9_DIO

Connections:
/OUT_P: C2.1, C3.1, D1.2 (A), J1.2, R1.1
/SOLAR_P: D2.2 (A), J4.1, Q1.1 (G), R4.1
GNDD: C1.2, C2.2, J1.1, J2.2, J4.2, Q1.2 (S), R2.2, R4.2, U1.2 (GND)
unnamed: D1.1 (K), L1.2, U1.1 (SW)
unnamed: D2.1 (K), J2.1, J3.2
unnamed: C1.1, J3.1, L1.1, R3.2, U1.5 (VIN)
unnamed: Q1.3 (D), R3.1, U1.4 (SHDN)
unnamed: C3.2, R1.2, R2.1, U1.3 (FB)
